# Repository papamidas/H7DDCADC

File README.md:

# H7DDCADC
A direct conversion software defined radio (SDR) for the shortwave range   

work in progress

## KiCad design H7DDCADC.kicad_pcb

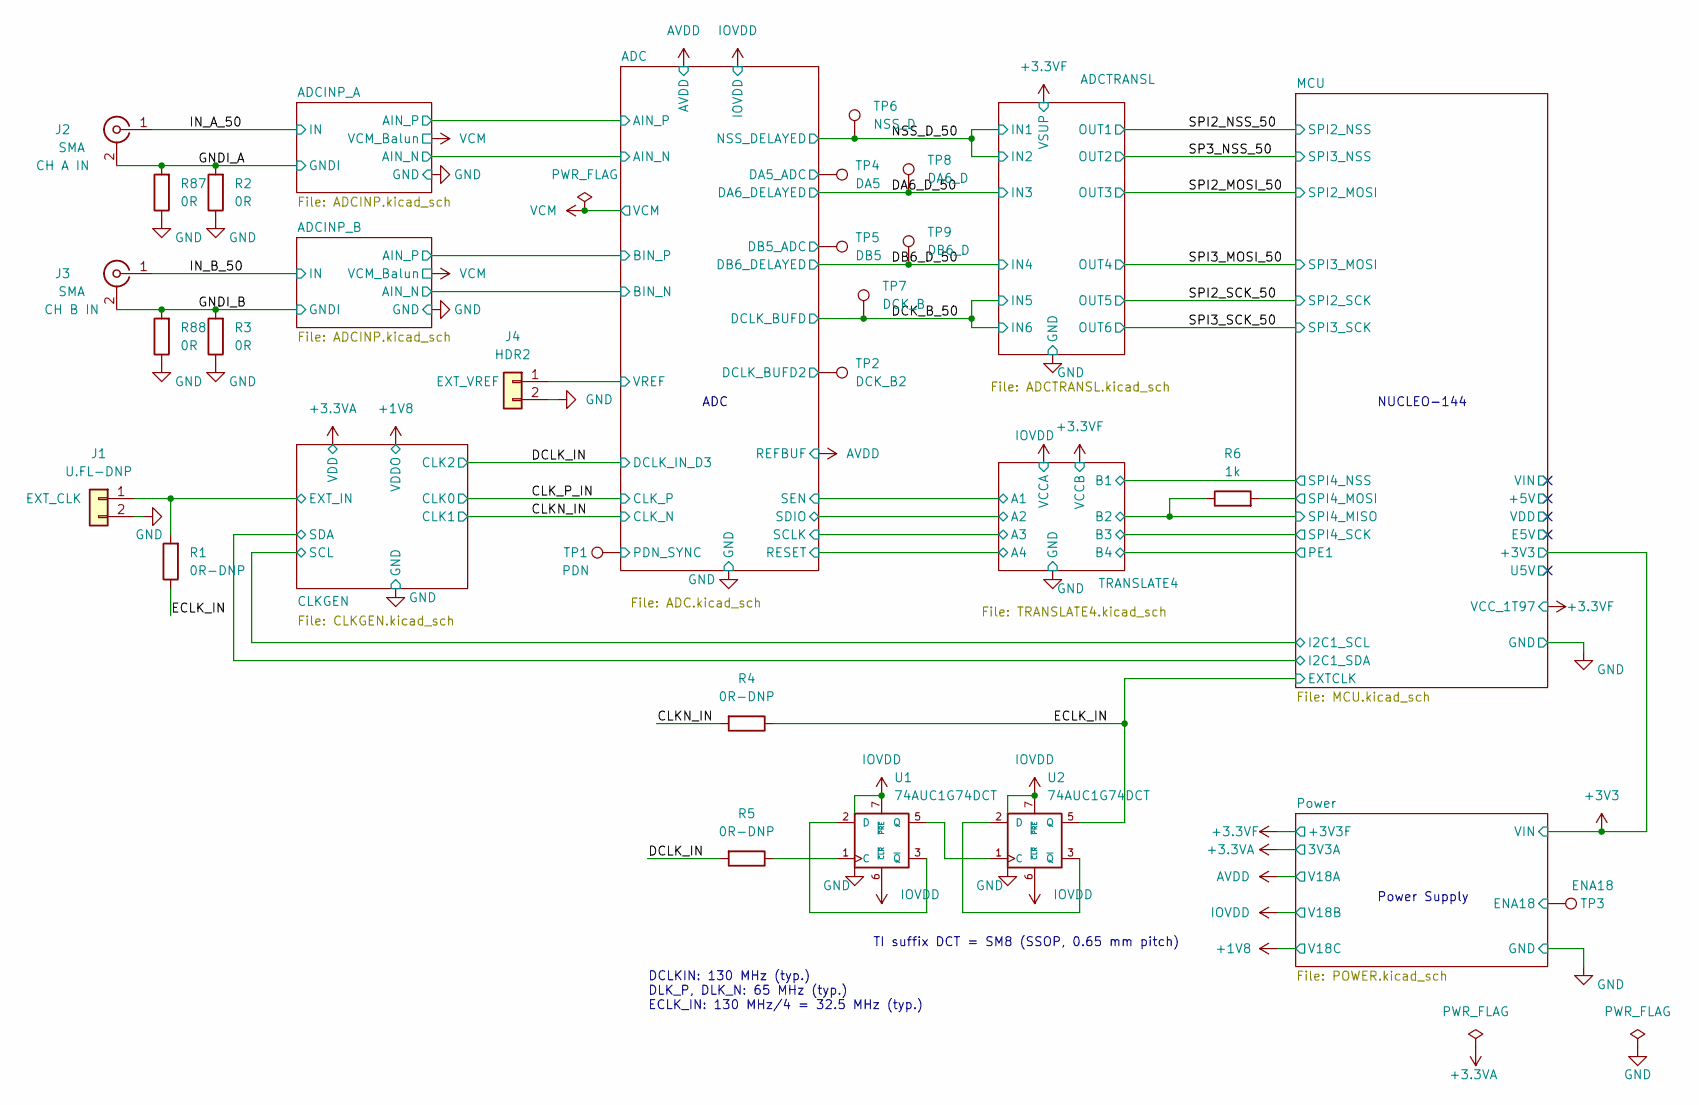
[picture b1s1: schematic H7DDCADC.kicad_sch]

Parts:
J1: U.FL-DNP; U.FL_Hirose_U.FL-R-SMT-1_Vertical
J2, J3: SMA; SMA_Wurth_60312002114503_Vertical
J4: HDR2; PinHeader_1x02_P2.54mm_Vertical
R1, R4, R5: 0R-DNP; R_0805_2012Metric
R2, R3, R87, R88: 0R; R_0805_2012Metric
R6: 1k; R_0805_2012Metric
TP1: PDN; TestPoint_THTPad_D1.5mm_Drill0.7mm
TP2: DCK_B2; TestPoint_THTPad_D1.5mm_Drill0.7mm
TP3: ENA18; TestPoint_THTPad_D1.5mm_Drill0.7mm
TP4: DA5; TestPoint_THTPad_D1.5mm_Drill0.7mm
TP5: DB5; TestPoint_THTPad_D1.5mm_Drill0.7mm
TP6: NSS_D; TestPoint_THTPad_D1.5mm_Drill0.7mm
TP7: DCK_B; TestPoint_THTPad_D1.5mm_Drill0.7mm
TP8: DA6_D; TestPoint_THTPad_D1.5mm_Drill0.7mm
TP9: DB6_D; TestPoint_THTPad_D1.5mm_Drill0.7mm
U1, U2: 74AUC1G74DCT; VSSOP-8_2.4x2.1mm_P0.5mm

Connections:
/ADC/DA5_ADC: TP4.1; also elsewhere on the board
/ADC/DB5_ADC: TP5.1; also elsewhere on the board
/ADC/DCLK_BUFD2: TP2.1; also elsewhere on the board
/ADC/PDN_SYNC: TP1.1; also elsewhere on the board
/ADC/VREF: J4.1; also elsewhere on the board
/CLKGEN/EXT_IN: J1.1, R1.2; also elsewhere on the board
/CLKN_IN: R4.2; also elsewhere on the board
/DA6_D_50: TP8.1; also elsewhere on the board
/DB6_D_50: TP9.1; also elsewhere on the board
/DCK_B_50: TP7.1; also elsewhere on the board
/DCLK_IN: R5.2; also elsewhere on the board
/ECLK_IN: R1.1, R4.1, U2.5 (Q); also elsewhere on the board
/GNDI_A: J2.2 (Ext), R2.2, R87.2; also elsewhere on the board
/GNDI_B: J3.2 (Ext), R3.2, R88.2; also elsewhere on the board
/IN_A_50: J2.1 (In); also elsewhere on the board
/IN_B_50: J3.1 (In); also elsewhere on the board
/MCU/SPI4_MISO: R6.1; also elsewhere on the board
/MCU/SPI4_MOSI: R6.2; also elsewhere on the board
/NSS_D_50: TP6.1; also elsewhere on the board
/Power/ENA18: TP3.1; also elsewhere on the board
GND: J1.2, J4.2, R2.1, R3.1, R87.1, R88.1, U1.4 (GND), U2.4 (GND); also elsewhere on the board
IOVDD: U1.6 (~CLR), U1.7 (~PRE), U1.8 (VCC), U2.6 (~CLR), U2.7 (~PRE), U2.8 (VCC); also elsewhere on the board
unnamed: R5.1, U1.1 (C)
unnamed: U1.2 (D), U1.3 (~Q)
unnamed: U1.5 (Q), U2.1 (C)
unnamed: U2.2 (D), U2.3 (~Q)

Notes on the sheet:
Power Supply
NUCLEO-144
DCLKIN: 130 MHz (typ.) DLK_P, DLK_N: 65 MHz (typ.) ECLK_IN: 130 MHz/4 = 32.5 MHz (typ.)
TI suffix DCT = SM8 (SSOP, 0.65 mm pitch)
ADC

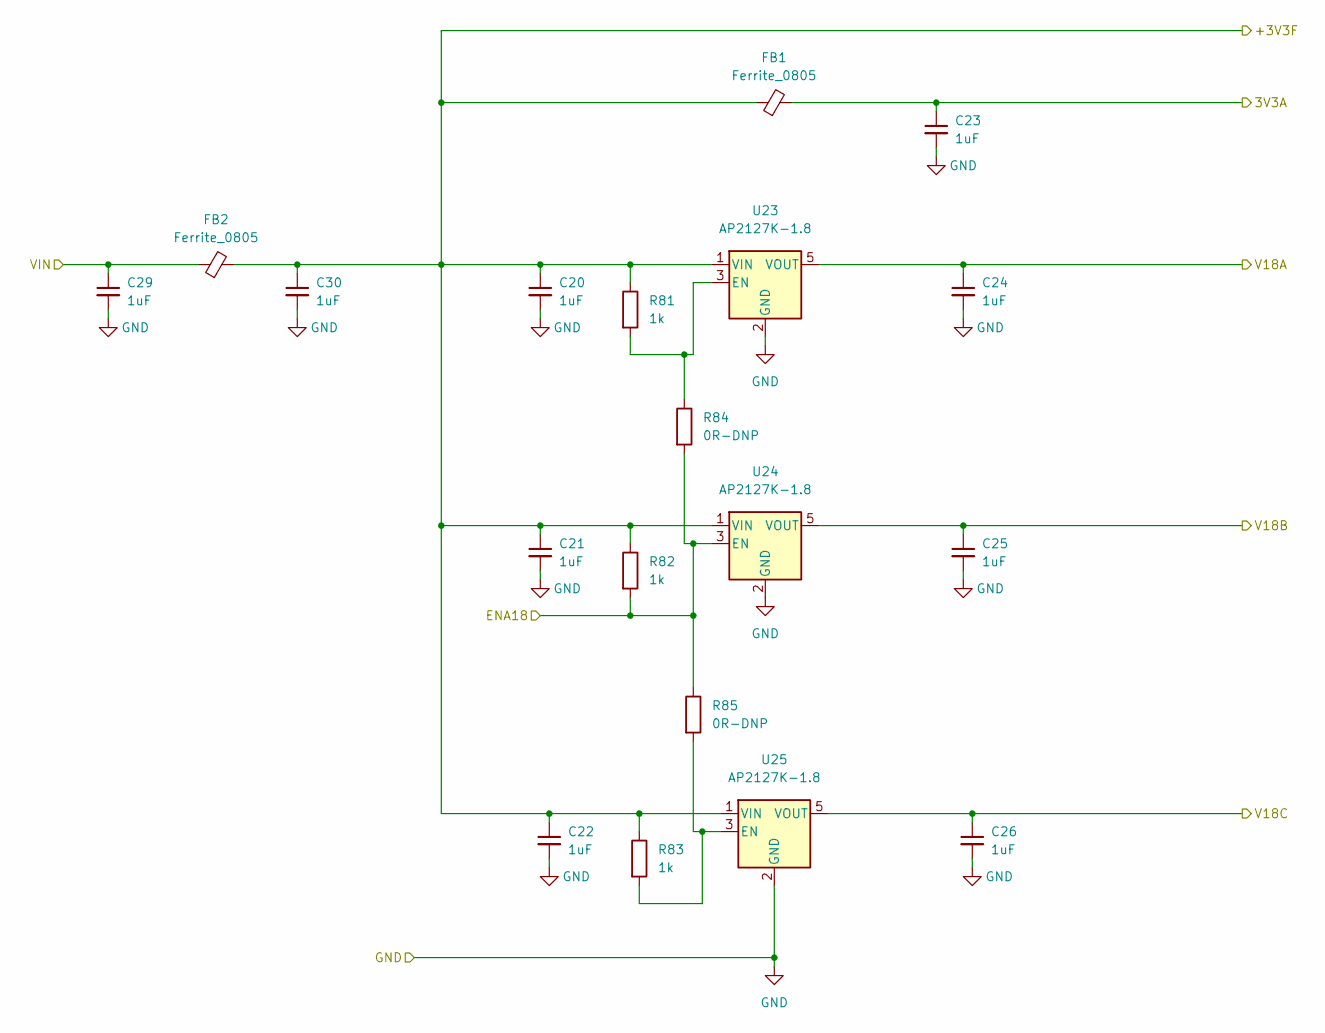
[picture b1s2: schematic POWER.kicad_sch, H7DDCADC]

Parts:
C20, C21, C22, C23, C24, C25, C26, C29, C30: 1uF; C_0805_2012Metric
FB1, FB2: Ferrite_0805; R_0805_2012Metric
R81, R82, R83: 1k; R_0805_2012Metric
R84, R85: 0R-DNP; R_0805_2012Metric
U23, U24, U25: AP2127K-1.8; SOT-23-5

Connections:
+1V8: C26.1, U25.5 (VOUT); also elsewhere on the board
+3.3VF: C20.1, C21.1, C22.1, C30.1, FB1.1, FB2.2, R81.1, R82.1, R83.1, U23.1 (VIN), U24.1 (VIN), U25.1 (VIN); also elsewhere on the board
+3V3: C29.1, FB2.1; also elsewhere on the board
/Power/ENA18: R82.2, R84.2, R85.1, U24.3 (EN); also elsewhere on the board
AVDD: C24.1, U23.5 (VOUT); also elsewhere on the board
GND: C20.2, C21.2, C22.2, C23.2, C24.2, C25.2, C26.2, C29.2, C30.2, U23.2 (GND), U24.2 (GND), U25.2 (GND); also elsewhere on the board
IOVDD: C25.1, U24.5 (VOUT); also elsewhere on the board
unnamed: R81.2, R84.1, U23.3 (EN)
unnamed: R83.2, R85.2, U25.3 (EN)

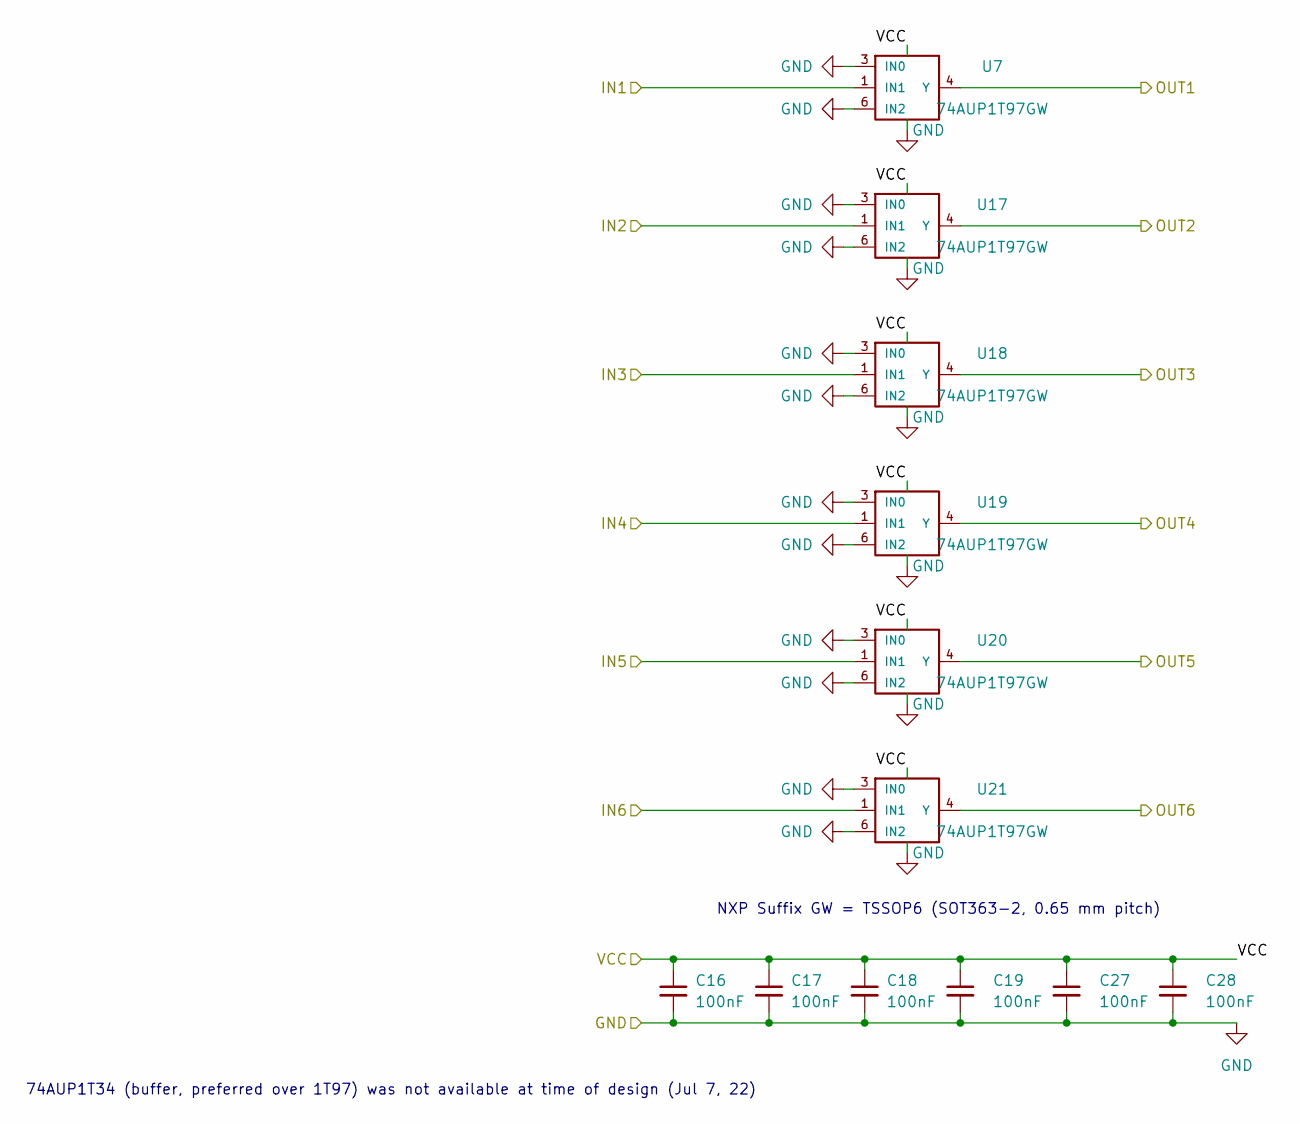
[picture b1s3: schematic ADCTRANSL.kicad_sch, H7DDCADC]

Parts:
C16, C17, C18, C19, C27, C28: 100nF; C_0805_2012Metric
U7, U17, U18, U19, U20, U21: 74AUP1T97GW; SOT-363_SC-70-6_Handsoldering

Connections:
/DA6_D_50: U18.1 (IN1); also elsewhere on the board
/DB6_D_50: U19.1 (IN1); also elsewhere on the board
/DCK_B_50: U20.1 (IN1), U21.1 (IN1); also elsewhere on the board
/NSS_D_50: U7.1 (IN1), U17.1 (IN1); also elsewhere on the board
/SP3_NSS_50: U17.4 (Y); also elsewhere on the board
/SPI2_MOSI_50: U18.4 (Y); also elsewhere on the board
/SPI2_NSS_50: U7.4 (Y); also elsewhere on the board
/SPI2_SCK_50: U20.4 (Y); also elsewhere on the board
/SPI3_MOSI_50: U19.4 (Y); also elsewhere on the board
/SPI3_SCK_50: U21.4 (Y); also elsewhere on the board
GND: C16.2, C17.2, C18.2, C19.2, C27.2, C28.2, U7.2 (GND), U7.3 (IN0), U7.6 (IN2), U17.2 (GND), U17.3 (IN0), U17.6 (IN2), U18.2 (GND), U18.3 (IN0), U18.6 (IN2), U19.2 (GND), U19.3 (IN0), U19.6 (IN2), U20.2 (GND), U20.3 (IN0), U20.6 (IN2), U21.2 (GND), U21.3 (IN0), U21.6 (IN2); also elsewhere on the board
V1T97: C16.1, C17.1, C18.1, C19.1, C27.1, C28.1, U7.5 (VCC), U17.5 (VCC), U18.5 (VCC), U19.5 (VCC), U20.5 (VCC), U21.5 (VCC); also elsewhere on the board

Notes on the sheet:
74AUP1T34 (buffer, preferred over 1T97) was not available at time of design (Jul 7, 22)
NXP Suffix GW = TSSOP6 (SOT363-2, 0.65 mm pitch)

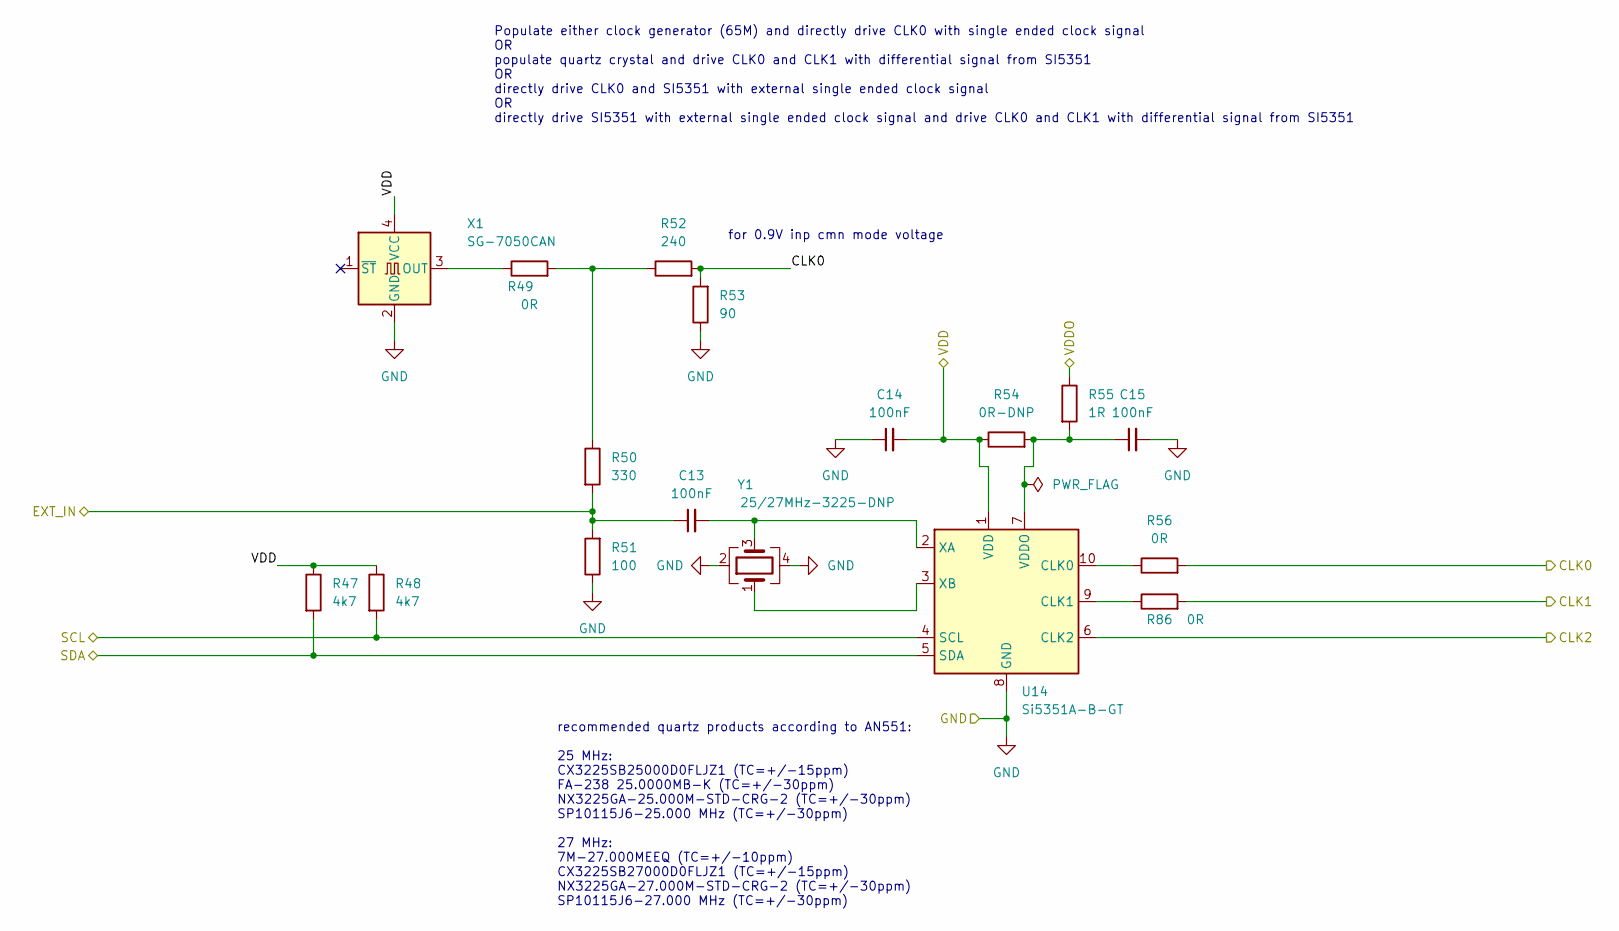
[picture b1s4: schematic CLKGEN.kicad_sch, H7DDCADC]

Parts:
C13, C14, C15: 100nF; C_0805_2012Metric
R47, R48: 4k7; R_0805_2012Metric
R49, R56, R86: 0R; R_0805_2012Metric
R50: 330; R_0805_2012Metric
R51: 100; R_0805_2012Metric
R52: 240; R_0805_2012Metric
R53: 90; R_0805_2012Metric
R54: 0R-DNP; R_0805_2012Metric
R55: 1R; R_0805_2012Metric
U14: Si5351A-B-GT; MSOP-10_3x3mm_P0.5mm
X1: SG-7050CAN; Oscillator_SMD_SeikoEpson_SG8002CA-4Pin_7.0x5.0mm
Y1: 25/27MHz-3225-DNP; Crystal_SMD_3225-4Pin_3.2x2.5mm_HandSoldering

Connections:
+1V8: R55.1; also elsewhere on the board
/CLKGEN/EXT_IN: C13.1, R50.2, R51.2; also elsewhere on the board
/CLKGEN/SCL: R48.2, U14.4 (SCL); also elsewhere on the board
/CLKGEN/SDA: R47.2, U14.5 (SDA); also elsewhere on the board
/CLKN_IN: R86.2; also elsewhere on the board
/CLK_P_IN: R52.2, R53.2, R56.2; also elsewhere on the board
/DCLK_IN: U14.6 (CLK2); also elsewhere on the board
GND: C14.1, C15.2, R51.1, R53.1, U14.8 (GND), X1.2 (GND), Y1.2, Y1.4; also elsewhere on the board
unnamed: C13.2, U14.2 (XA), Y1.3
unnamed: C15.1, R54.2, R55.2, U14.7 (VDDO)
unnamed: R49.1, X1.3 (OUT)
unnamed: R49.2, R50.1, R52.1
unnamed: R56.1, U14.10 (CLK0)
unnamed: R86.1, U14.9 (CLK1)
unnamed: U14.3 (XB), Y1.1

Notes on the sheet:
Populate either clock generator (65M) and directly drive CLK0 with single ended clock signal OR populate quartz crystal and drive CLK0 and CLK1 with differential signal from SI5351 OR directly drive CLK0 and SI5351 with external single ended clock signal OR directly drive SI5351 with external singl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
for 0.9V inp cmn mode voltage
recommended quartz products according to AN551: 25 MHz: CX3225SB25000D0FLJZ1 (TC=+/-15ppm) FA-238 25.0000MB-K (TC=+/-30ppm) NX3225GA-25.000M-STD-CRG-2 (TC=+/-30ppm) SP10115J6-25.000 MHz (TC=+/-30ppm) 27 MHz: 7M-27.000MEEQ (TC=+/-10ppm) CX3225SB27000D0FLJZ1 (TC=+/-15ppm) NX3225GA-27.000M-STD-CRG-2 (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

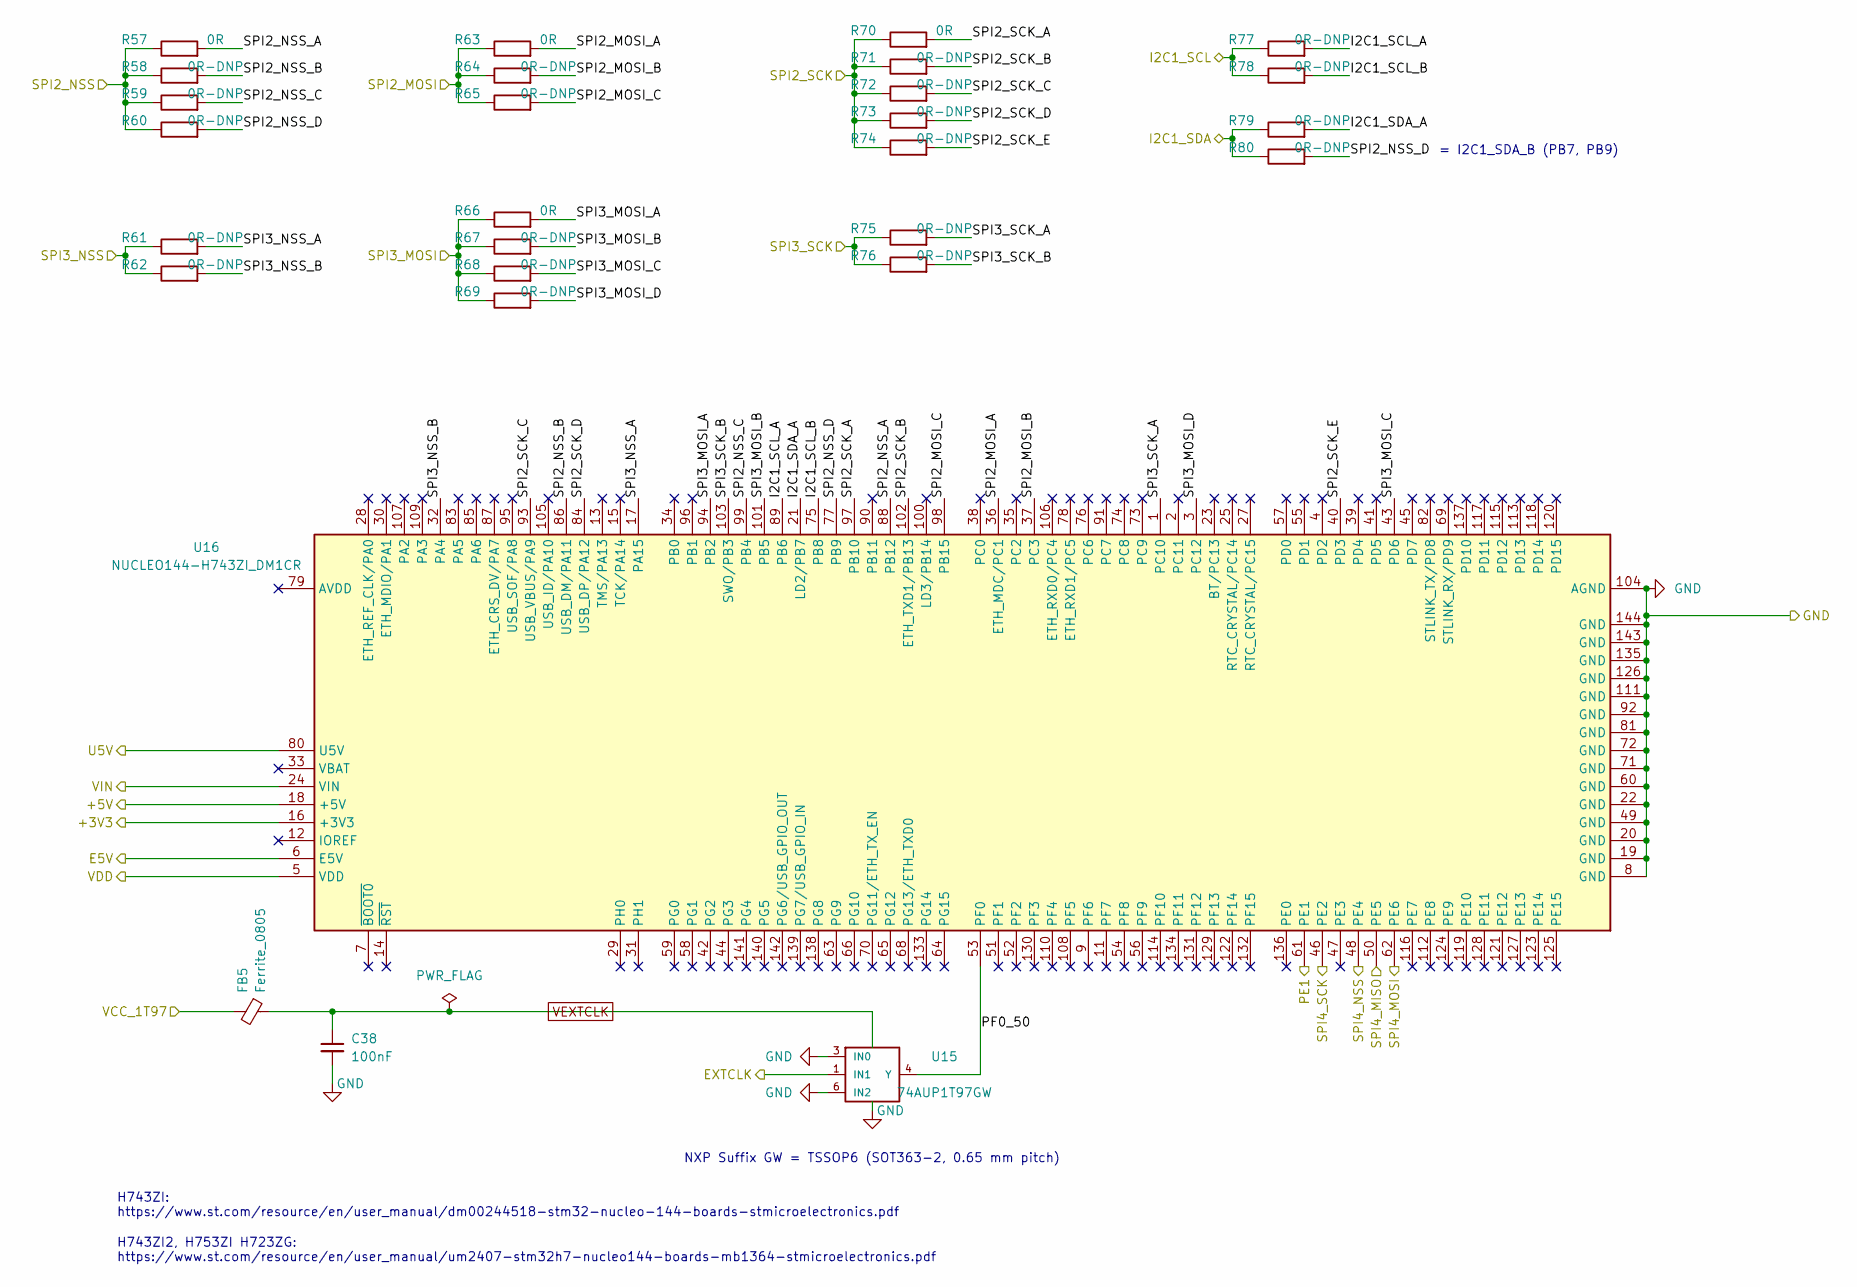
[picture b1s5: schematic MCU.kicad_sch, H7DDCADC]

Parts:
C38: 100nF; C_0805_2012Metric
FB5: Ferrite_0805; R_0805_2012Metric
R57, R63, R66, R70: 0R; R_0402_1005Metric_Pad0.72x0.64mm_HandSolder
R58, R59, R60, R61, R62, R64, R65, R67, R68, R69, R71, R72, R73, R74, R75, R76, R77, R78, R79, R80: 0R-DNP; R_0402_1005Metric_Pad0.72x0.64mm_HandSolder
U15: 74AUP1T97GW; SOT-363_SC-70-6_Handsoldering
U16: NUCLEO144-H743ZI_DM1CR; ST_Morpho_Connector_144_STLink

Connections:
+3.3VF: FB5.2; also elsewhere on the board
+3V3: U16.16 (+3V3); also elsewhere on the board
/CLKGEN/SCL: R77.1, R78.1; also elsewhere on the board
/CLKGEN/SDA: R79.1, R80.1; also elsewhere on the board
/ECLK_IN: U15.1 (IN1); also elsewhere on the board
/MCU/+5V: U16.18 (+5V); also elsewhere on the board
/MCU/E5V: U16.6 (E5V); also elsewhere on the board
/MCU/I2C1_SCL_A: R77.2, U16.89 (PB6); also elsewhere on the board
/MCU/I2C1_SCL_B: R78.2, U16.75 (PB8); also elsewhere on the board
/MCU/I2C1_SDA_A: R79.2, U16.21 (LD2/PB7); also elsewhere on the board
/MCU/PE1: U16.61 (PE1); also elsewhere on the board
/MCU/PF0_50: U15.4 (Y), U16.53 (PF0); also elsewhere on the board
/MCU/SPI2_MOSI_A: R63.2, U16.36 (ETH_MDC/PC1); also elsewhere on the board
/MCU/SPI2_MOSI_B: R64.2, U16.37 (PC3); also elsewhere on the board
/MCU/SPI2_MOSI_C: R65.2, U16.98 (PB15); also elsewhere on the board
/MCU/SPI2_NSS_A: R57.2, U16.88 (PB12); also elsewhere on the board
/MCU/SPI2_NSS_B: R58.2, U16.86 (USB_DM/PA11); also elsewhere on the board
/MCU/SPI2_NSS_C: R59.2, U16.99 (PB4); also elsewhere on the board
/MCU/SPI2_NSS_D: R60.2, R80.2, U16.77 (PB9); also elsewhere on the board
/MCU/SPI2_SCK_A: R70.2, U16.97 (PB10); also elsewhere on the board
/MCU/SPI2_SCK_B: R71.2, U16.102 (ETH_TXD1/PB13); also elsewhere on the board
/MCU/SPI2_SCK_C: R72.2, U16.93 (USB_VBUS/PA9); also elsewhere on the board
/MCU/SPI2_SCK_D: R73.2, U16.84 (USB_DP/PA12); also elsewhere on the board
/MCU/SPI2_SCK_E: R74.2, U16.40 (PD3); also elsewhere on the board
/MCU/SPI3_MOSI_A: R66.2, U16.94 (PB2); also elsewhere on the board
/MCU/SPI3_MOSI_B: R67.2, U16.101 (PB5); also elsewhere on the board
/MCU/SPI3_MOSI_C: R68.2, U16.43 (PD6); also elsewhere on the board
/MCU/SPI3_MOSI_D: R69.2, U16.3 (PC12); also elsewhere on the board
/MCU/SPI3_NSS_A: R61.2, U16.17 (PA15); also elsewhere on the board
/MCU/SPI3_NSS_B: R62.2, U16.32 (PA4); also elsewhere on the board
/MCU/SPI3_SCK_A: R75.2, U16.1 (PC10); also elsewhere on the board
/MCU/SPI3_SCK_B: R76.2, U16.103 (SWO/PB3); also elsewhere on the board
/MCU/SPI4_MISO: U16.50 (PE5); also elsewhere on the board
/MCU/SPI4_MOSI: U16.62 (PE6); also elsewhere on the board
/MCU/SPI4_NSS: U16.48 (PE4); also elsewhere on the board
/MCU/SPI4_SCK: U16.46 (PE2); also elsewhere on the board
/MCU/U5V: U16.80 (U5V); also elsewhere on the board
/MCU/VDD: U16.5 (VDD); also elsewhere on the board
/MCU/VIN: U16.24 (VIN); also elsewhere on the board
/SP3_NSS_50: R61.1, R62.1; also elsewhere on the board
/SPI2_MOSI_50: R63.1, R64.1, R65.1; also elsewhere on the board
/SPI2_NSS_50: R57.1, R58.1, R59.1, R60.1; also elsewhere on the board
/SPI2_SCK_50: R70.1, R71.1, R72.1, R73.1, R74.1; also elsewhere on the board
/SPI3_MOSI_50: R66.1, R67.1, R68.1, R69.1; also elsewhere on the board
/SPI3_SCK_50: R75.1, R76.1; also elsewhere on the board
GND: C38.2, U15.2 (GND), U15.3 (IN0), U15.6 (IN2), U16.8 (GND), U16.19 (GND), U16.20 (GND), U16.22 (GND), U16.49 (GND), U16.60 (GND), U16.71 (GND), U16.72 (GND), U16.81 (GND), U16.92 (GND), U16.104 (AGND), U16.111 (GND), U16.126 (GND), U16.135 (GND), U16.143 (GND), U16.144 (GND); also elsewhere on the board
VEXTCLK: C38.1, FB5.1, U15.5 (VCC)

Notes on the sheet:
= I2C1_SDA_B (PB7, PB9)
NXP Suffix GW = TSSOP6 (SOT363-2, 0.65 mm pitch)
H743ZI2, H753ZI H723ZG: https://www.st.com/resource/en/user_manual/um2407-stm32h7-nucleo144-boards-mb1364-stmicroelectronics.pdf
H743ZI: https://www.st.com/resource/en/user_manual/dm00244518-stm32-nucleo-144-boards-stmicroelectronics.pdf

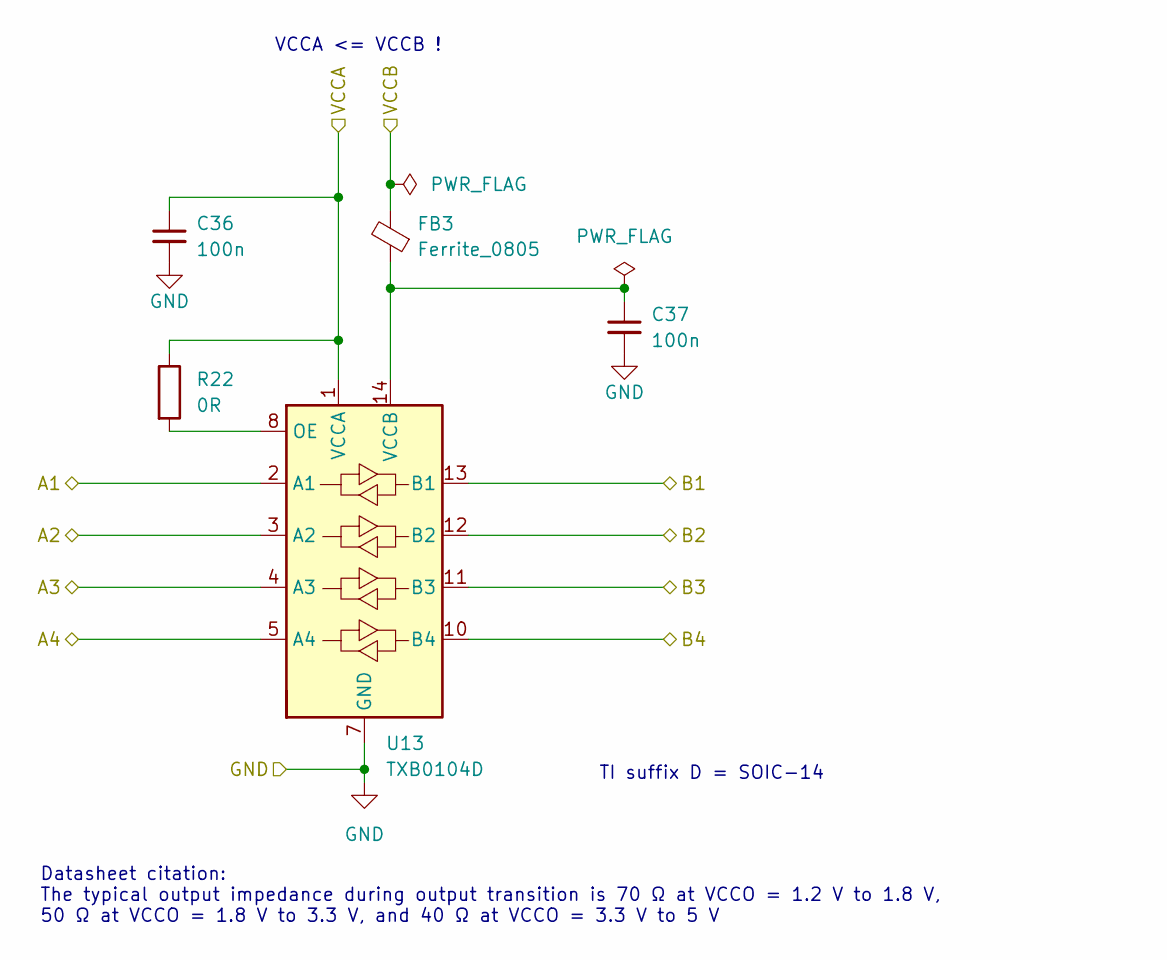
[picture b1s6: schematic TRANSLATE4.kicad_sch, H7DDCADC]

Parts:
C36, C37: 100n; C_0402_1005Metric_Pad0.74x0.62mm_HandSolder
FB3: Ferrite_0805; R_0805_2012Metric
R22: 0R; R_0805_2012Metric
U13: TXB0104D; SOIC-14_3.9x8.7mm_P1.27mm

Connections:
/ADC/RESET: U13.5 (A4); also elsewhere on the board
/ADC/SCLK: U13.4 (A3); also elsewhere on the board
/ADC/SDIO: U13.3 (A2); also elsewhere on the board
/ADC/SEN: U13.2 (A1); also elsewhere on the board
/MCU/PE1: U13.10 (B4); also elsewhere on the board
/MCU/SPI4_MISO: U13.12 (B2); also elsewhere on the board
/MCU/SPI4_NSS: U13.13 (B1); also elsewhere on the board
/MCU/SPI4_SCK: U13.11 (B3); also elsewhere on the board
GND: C36.2, C37.2, U13.7 (GND); also elsewhere on the board
IOVDD: C36.1, R22.1, U13.1 (VCCA); also elsewhere on the board
unnamed: R22.2, U13.8 (OE)

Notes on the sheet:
TI suffix D = SOIC-14
Datasheet citation: The typical output impedance during output transition is 70 Ω at VCCO = 1.2 V to 1.8 V, 50 Ω at VCCO = 1.8 V to 3.3 V, and 40 Ω at VCCO = 3.3 V to 5 V
VCCA <= VCCB !

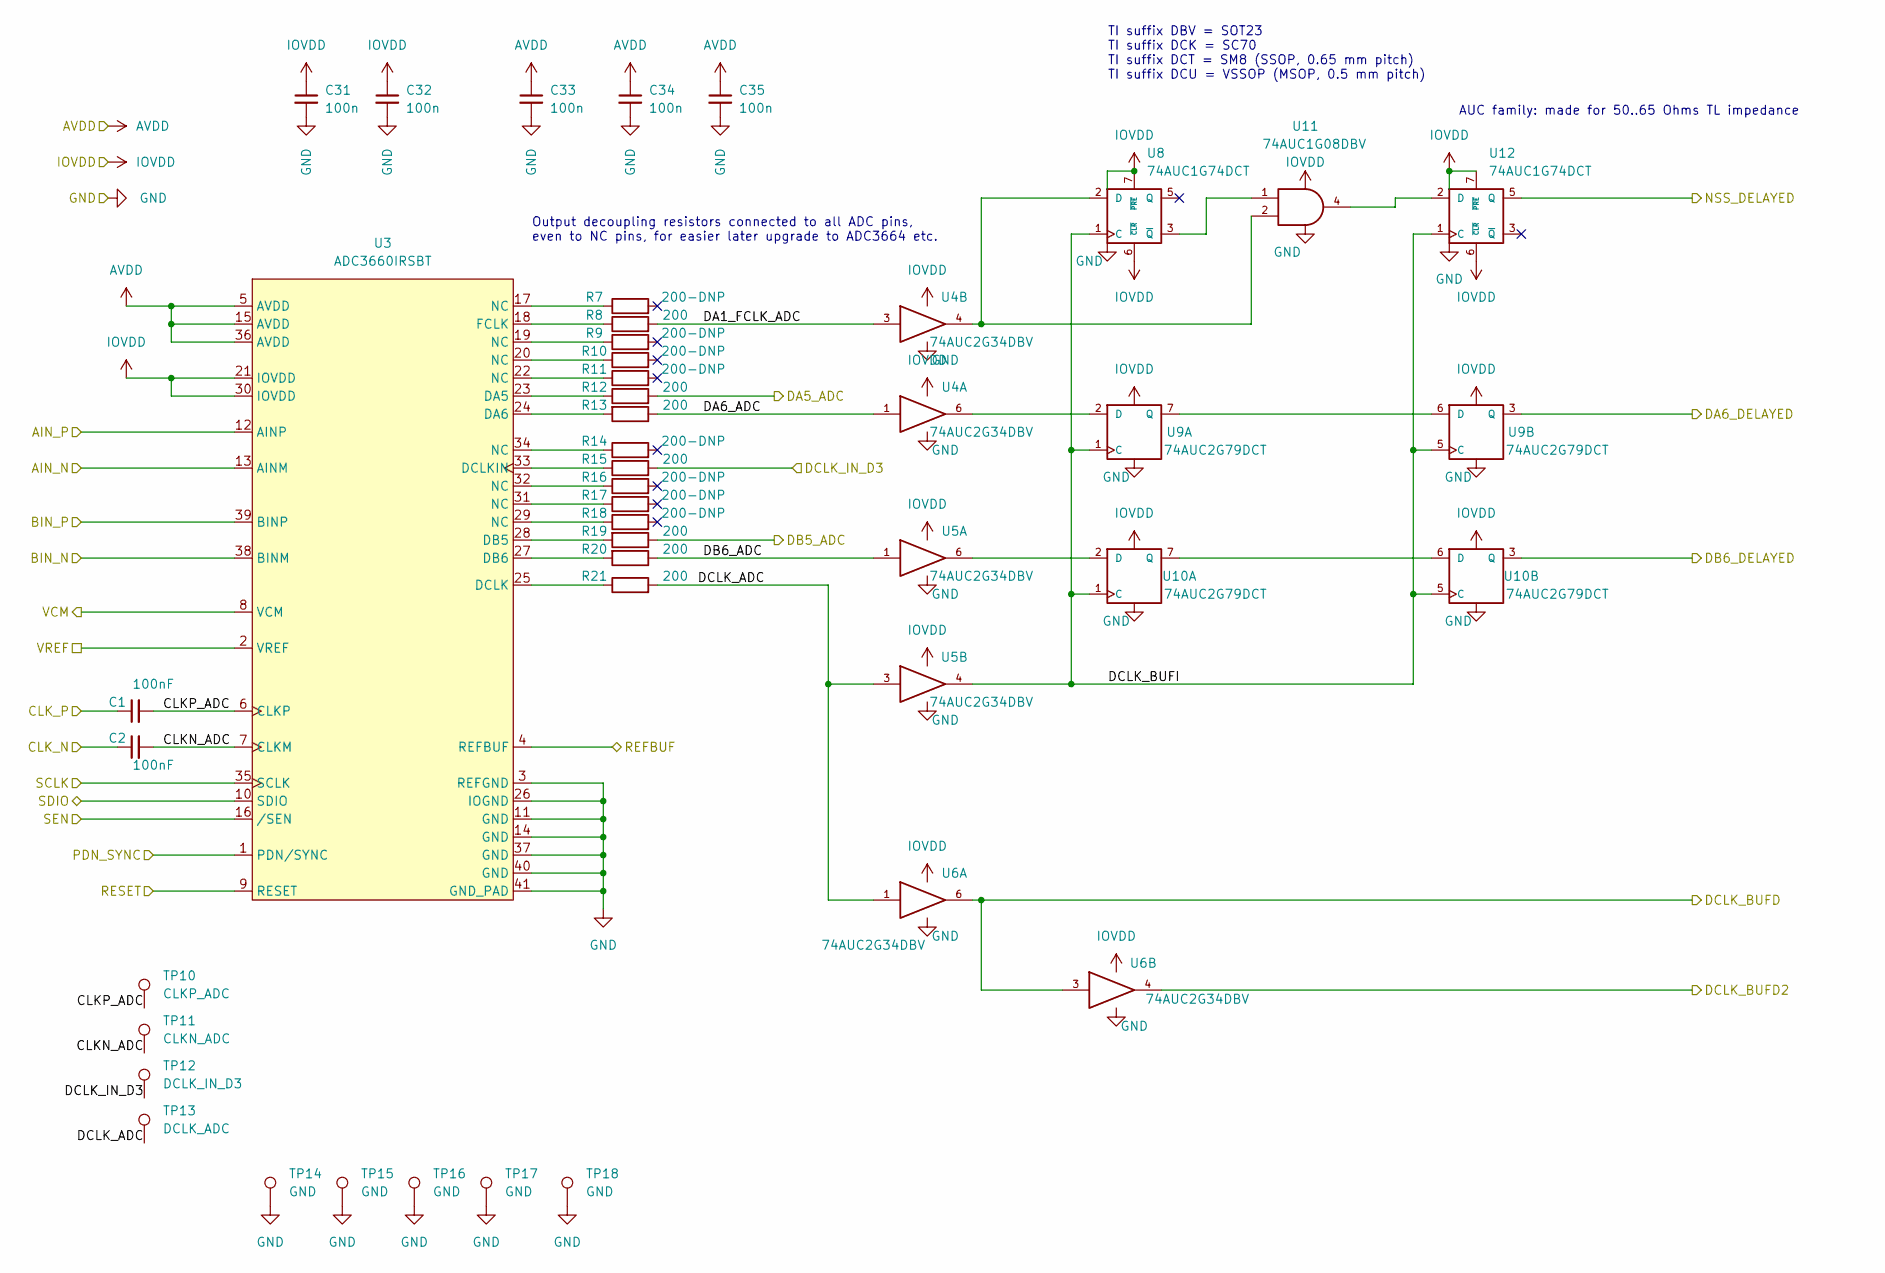
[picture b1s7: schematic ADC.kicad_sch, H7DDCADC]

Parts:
C1, C2: 100nF; C_0805_2012Metric
C31, C32, C33, C34, C35: 100n; C_0402_1005Metric_Pad0.74x0.62mm_HandSolder
R7, R9, R10, R11, R14, R16, R17, R18: 200-DNP; R_0402_1005Metric_Pad0.72x0.64mm_HandSolder
R8, R12, R13, R15, R19, R20, R21: 200; R_0402_1005Metric_Pad0.72x0.64mm_HandSolder
TP10: CLKP_ADC; TestPoint_THTPad_D1.5mm_Drill0.7mm
TP11: CLKN_ADC; TestPoint_THTPad_D1.5mm_Drill0.7mm
TP12: DCLK_IN_D3; TestPoint_THTPad_D1.5mm_Drill0.7mm
TP13: DCLK_ADC; TestPoint_THTPad_D1.5mm_Drill0.7mm
TP14, TP15, TP16, TP17, TP18: GND; TestPoint_THTPad_D1.5mm_Drill0.7mm
U3: ADC3660IRSBT; QFN-40-1EP_5x5mm_P0.4mm_EP3.6x3.6mm
U4, U5, U6: 74AUC2G34DBV; SOT-23-6_Handsoldering
U8, U12: 74AUC1G74DCT; VSSOP-8_2.4x2.1mm_P0.5mm
U9, U10: 74AUC2G79DCT; MSOP-8_3x3mm_P0.65mm
U11: 74AUC1G08DBV; SOT-23-5

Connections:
/ADC/AIN_N: U3.13 (AINM); also elsewhere on the board
/ADC/AIN_P: U3.12 (AINP); also elsewhere on the board
/ADC/BIN_N: U3.38 (BINM); also elsewhere on the board
/ADC/BIN_P: U3.39 (BINP); also elsewhere on the board
/ADC/CLKN_ADC: C2.2, TP11.1, U3.7 (CLKM); also elsewhere on the board
/ADC/CLKP_ADC: C1.2, TP10.1, U3.6 (CLKP); also elsewhere on the board
/ADC/DA1_FCLK_ADC: R8.2, U4.3
/ADC/DA5_ADC: R12.2; also elsewhere on the board
/ADC/DA6_ADC: R13.1, U4.1
/ADC/DB5_ADC: R19.1; also elsewhere on the board
/ADC/DB6_ADC: R20.1, U5.1
/ADC/DCLK_ADC: R21.2, TP13.1, U5.3, U6.1
/ADC/DCLK_BUFD2: U6.4; also elsewhere on the board
/ADC/DCLK_BUFI: U5.4, U8.1 (C), U9.1 (C), U9.5 (C), U10.1 (C), U10.5 (C), U12.1 (C)
/ADC/PDN_SYNC: U3.1 (PDN/SYNC); also elsewhere on the board
/ADC/RESET: U3.9 (RESET); also elsewhere on the board
/ADC/SCLK: U3.35 (SCLK); also elsewhere on the board
/ADC/SDIO: U3.10 (SDIO); also elsewhere on the board
/ADC/SEN: U3.16 (/SEN); also elsewhere on the board
/ADC/VREF: U3.2 (VREF); also elsewhere on the board
/CLKN_IN: C2.1; also elsewhere on the board
/CLK_P_IN: C1.1; also elsewhere on the board
/DA6_D_50: U9.3 (Q); also elsewhere on the board
/DB6_D_50: U10.3 (Q); also elsewhere on the board
/DCK_B_50: U6.3, U6.6; also elsewhere on the board
/DCLK_IN: R15.2, TP12.1; also elsewhere on the board
/NSS_D_50: U12.5 (Q); also elsewhere on the board
AVDD: C33.1, C34.1, C35.1, U3.4 (REFBUF), U3.5 (AVDD), U3.15 (AVDD), U3.36 (AVDD); also elsewhere on the board
GND: C31.2, C32.2, C33.2, C34.2, C35.2, TP14.1, TP15.1, TP16.1, TP17.1, TP18.1, U3.3 (REFGND), U3.11 (GND), U3.14 (GND), U3.26 (IOGND), U3.37 (GND), U3.40 (GND), U3.41 (GND_PAD), U4.2 (GND), U5.2 (GND), U6.2 (GND), U8.4 (GND), U9.4 (GND), U10.4 (GND), U11.3 (GND), U12.4 (GND); also elsewhere on the board
IOVDD: C31.1, C32.1, U3.21 (IOVDD), U3.30 (IOVDD), U4.5 (VCC), U5.5 (VCC), U6.5 (VCC), U8.6 (~CLR), U8.7 (~PRE), U8.8 (VCC), U9.8 (VCC), U10.8 (VCC), U11.5 (VCC), U12.6 (~CLR), U12.7 (~PRE), U12.8 (VCC); also elsewhere on the board
unnamed 107: R7.1, U3.17 (NC); also elsewhere on the board
unnamed 108: R8.1, U3.18 (FCLK); also elsewhere on the board
unnamed 109: R9.1, U3.19 (NC); also elsewhere on the board
unnamed 110: R10.1, U3.20 (NC); also elsewhere on the board
unnamed 111: R11.1, U3.22 (NC); also elsewhere on the board
unnamed 112: R12.1, U3.23 (DA5); also elsewhere on the board
unnamed 113: R13.2, U3.24 (DA6); also elsewhere on the board
unnamed 114: R14.1, U3.34 (NC); also elsewhere on the board
unnamed 115: R15.1, U3.33 (DCLKIN); also elsewhere on the board
unnamed 116: R16.1, U3.32 (NC); also elsewhere on the board
unnamed 117: R17.1, U3.31 (NC); also elsewhere on the board
unnamed 118: R18.1, U3.29 (NC); also elsewhere on the board
unnamed 119: R19.2, U3.28 (DB5); also elsewhere on the board
unnamed 120: R20.2, U3.27 (DB6); also elsewhere on the board
unnamed 121: R21.1, U3.25 (DCLK); also elsewhere on the board
unnamed: U4.6, U9.2 (D)
unnamed: U9.6 (D), U9.7 (Q)
unnamed: U5.6, U10.2 (D)
unnamed: U10.6 (D), U10.7 (Q)
unnamed: U8.3 (~Q), U11.1
unnamed: U4.4, U8.2 (D), U11.2
unnamed: U11.4, U12.2 (D)
VCM: U3.8 (VCM); also elsewhere on the board

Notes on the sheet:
TI suffix DBV = SOT23 TI suffix DCK = SC70 TI suffix DCT = SM8 (SSOP, 0.65 mm pitch) TI suffix DCU = VSSOP (MSOP, 0.5 mm pitch)
Output decoupling resistors connected to all ADC pins, even to NC pins, for easier later upgrade to ADC3664 etc.
AUC family: made for 50..65 Ohms TL impedance

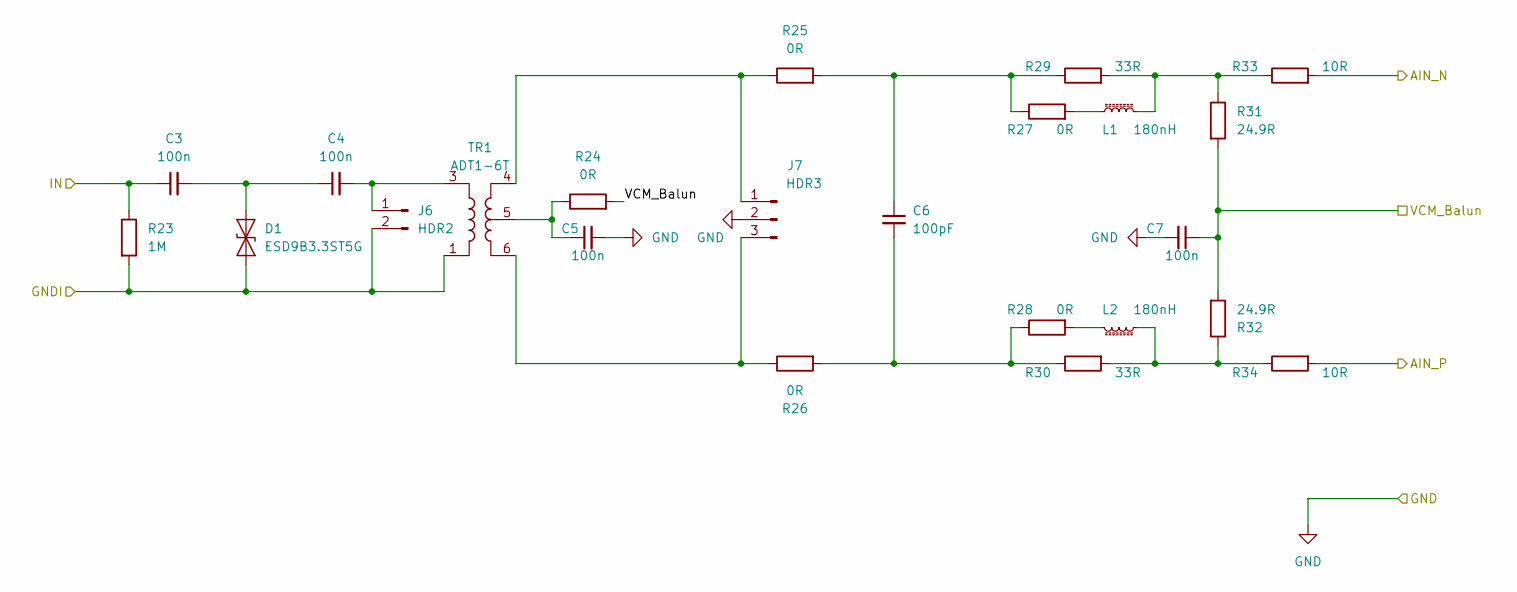
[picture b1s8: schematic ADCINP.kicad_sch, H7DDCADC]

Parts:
C3, C4, C5, C7: 100n; C_0805_2012Metric
C6: 100pF; C_0805_2012Metric
D1: ESD9B3.3ST5G; D_SOD-923
J6: HDR2; PinHeader_1x02_P2.54mm_Vertical
J7: HDR3; PinHeader_1x03_P2.54mm_Vertical
L1, L2: 180nH; R_0805_2012Metric
R23: 1M; R_0805_2012Metric
R24, R25, R26, R27, R28: 0R; R_0805_2012Metric
R29, R30: 33R; R_0805_2012Metric
R31, R32: 24.9R; R_0805_2012Metric
R33, R34: 10R; R_0805_2012Metric
TR1: ADT1-6T; Mini-Circuits_CD637_H5.23mm

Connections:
/ADC/AIN_N: R33.2; also elsewhere on the board
/ADC/AIN_P: R34.2; also elsewhere on the board
/GNDI_A: D1.1 (A1), J6.2, R23.2, TR1.1; also elsewhere on the board
/IN_A_50: C3.1, R23.1; also elsewhere on the board
GND: C5.2, C7.2, J7.2; also elsewhere on the board
unnamed: C3.2, C4.1, D1.2 (A2)
unnamed: C4.2, J6.1, TR1.3
unnamed: C5.1, R24.1, TR1.5
unnamed: C6.1, R25.2, R27.1, R29.1
unnamed: C6.2, R26.2, R28.1, R30.1
unnamed: J7.1, R25.1, TR1.4
unnamed: J7.3, R26.1, TR1.6
unnamed: L1.1, R27.2
unnamed: L1.2, R29.2, R31.1, R33.1
unnamed: L2.1, R28.2
unnamed: L2.2, R30.2, R32.1, R34.1
VCM: C7.1, R24.2, R31.2, R32.2; also elsewhere on the board

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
